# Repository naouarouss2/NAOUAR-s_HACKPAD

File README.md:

**NAOUAR's HACKPAD**

I do a lot of multitasking daily, and that also means that I use a lot of shortcuts, either to switch between apps, or to execute some programs, taks, and commands.
Some of the shortcuts can be pretty sketchy to get to, especially those that have buttons very far apart on the keyboard and require you to get your right hand off the mouse.
So to solve all of that, I decided to make a HACKPAD that has 12 programmable switches, a switch to switch between 4 keymaps, an encoder, an OLED display, and of course RGB.

I designed the PCB on KiCad, so here is the schematics :

And here is the PCB :

Everything will go inside this 3D Printed enclosure :

It will be mounted using M3*16 screws and heatset inserts just like shown below :

The bottom part of the enclosure will be printed in very thin white, or in transparent resin (if allowed), so that we can get the RGB underglow designed in the PCB.

The code is still untested, but I will test it as soon as I get my hands on the electronics, and correct the errors and do the mapping.

**BOM :**

1 SEED XIAO RP2040 (through-hole version)

13 MX switches

13 DSA Keycaps

1 EC11 Encoder

16 1N4148 Diodes

15 SK6812 Mini LEDs

1 0.91 inch 128*32 OLED Display

4 M3-16 screws

4 M3 heatset inserts

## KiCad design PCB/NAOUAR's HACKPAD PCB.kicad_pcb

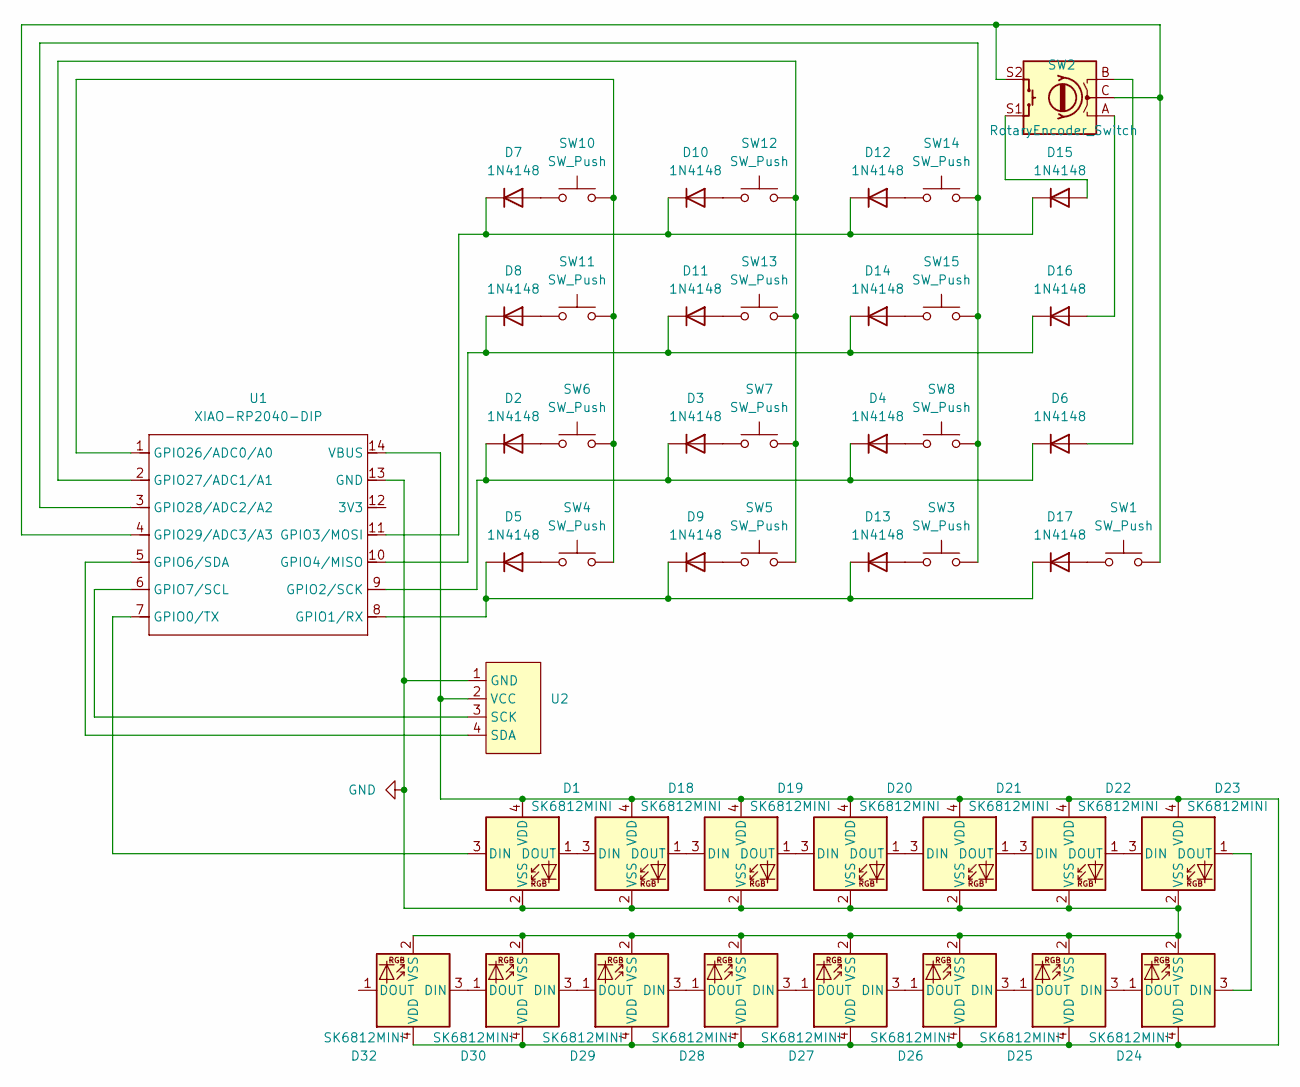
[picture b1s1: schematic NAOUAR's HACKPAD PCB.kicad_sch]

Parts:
D1, D18, D19, D20, D21, D22, D23, D24, D25, D26, D27, D28, D29, D30, D32: SK6812MINI; LED_SK6812MINI_PLCC4_3.5x3.5mm_P1.75mm
D2, D3, D4, D5, D6, D7, D8, D9, D10, D11, D12, D13, D14, D15, D16, D17: 1N4148; D_DO-35_SOD27_P7.62mm_Horizontal
SW1, SW3, SW4, SW5, SW6, SW7, SW8, SW10, SW11, SW12, SW13, SW14, SW15: SW_Push; SW_Cherry_MX_1.00u_PCB
SW2: RotaryEncoder_Switch; RotaryEncoder_Alps_EC11E-Switch_Vertical_H20mm
U1: XIAO-RP2040-DIP
U2: SSD1306-0.91-OLED-4pin-128x32

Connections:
GND: D1.2 (VSS), D18.2 (VSS), D19.2 (VSS), D20.2 (VSS), D21.2 (VSS), D22.2 (VSS), D23.2 (VSS), D24.2 (VSS), D25.2 (VSS), D26.2 (VSS), D27.2 (VSS), D28.2 (VSS), D29.2 (VSS), D30.2 (VSS), D32.2 (VSS), U1.13 (GND), U2.1 (GND)
unnamed: D1.3 (DIN), U1.7 (GPIO0/TX)
unnamed: D1.1 (DOUT), D18.3 (DIN)
unnamed: D1.4 (VDD), D18.4 (VDD), D19.4 (VDD), D20.4 (VDD), D21.4 (VDD), D22.4 (VDD), D23.4 (VDD), D24.4 (VDD), D25.4 (VDD), D26.4 (VDD), D27.4 (VDD), D28.4 (VDD), D29.4 (VDD), D30.4 (VDD), D32.4 (VDD), U1.14 (VBUS), U2.2 (VCC)
unnamed: D2.2 (A), SW6.1
unnamed: D2.1 (K), D3.1 (K), D4.1 (K), D6.1 (K), U1.9 (GPIO2/SCK)
unnamed: D3.2 (A), SW7.1
unnamed: D4.2 (A), SW8.1
unnamed: D5.2 (A), SW4.1
unnamed: D6.2 (A), SW2.B
unnamed: D7.2 (A), SW10.1
unnamed: D8.2 (A), SW11.1
unnamed: D9.2 (A), SW5.1
unnamed: D10.2 (A), SW12.1
unnamed: D7.1 (K), D10.1 (K), D12.1 (K), D15.1 (K), U1.11 (GPIO3/MOSI)
unnamed: D11.2 (A), SW13.1
unnamed: D8.1 (K), D11.1 (K), D14.1 (K), D16.1 (K), U1.10 (GPIO4/MISO)
unnamed: D12.2 (A), SW14.1
unnamed: D13.2 (A), SW3.1
unnamed: D5.1 (K), D9.1 (K), D13.1 (K), D17.1 (K), U1.8 (GPIO1/RX)
unnamed: D14.2 (A), SW15.1
unnamed: D15.2 (A), SW2.S1
unnamed: D16.2 (A), SW2.A
unnamed: D17.2 (A), SW1.1
unnamed: D18.1 (DOUT), D19.3 (DIN)
unnamed: D19.1 (DOUT), D20.3 (DIN)
unnamed: D20.1 (DOUT), D21.3 (DIN)
unnamed: D21.1 (DOUT), D22.3 (DIN)
unnamed: D22.1 (DOUT), D23.3 (DIN)
unnamed: D23.1 (DOUT), D24.3 (DIN)
unnamed: D24.1 (DOUT), D25.3 (DIN)
unnamed: D25.1 (DOUT), D26.3 (DIN)
unnamed: D26.1 (DOUT), D27.3 (DIN)
unnamed: D27.1 (DOUT), D28.3 (DIN)
unnamed: D28.1 (DOUT), D29.3 (DIN)
unnamed: D29.1 (DOUT), D30.3 (DIN)
unnamed: D30.1 (DOUT), D32.3 (DIN)
unnamed: U1.5 (GPIO6/SDA), U2.4 (SDA)
unnamed: U1.6 (GPIO7/SCL), U2.3 (SCK)
unnamed: SW4.2, SW6.2, SW10.2, SW11.2, U1.1 (GPIO26/ADC0/A0)
unnamed: SW5.2, SW7.2, SW12.2, SW13.2, U1.2 (GPIO27/ADC1/A1)
unnamed: SW3.2, SW8.2, SW14.2, SW15.2, U1.3 (GPIO28/ADC2/A2)
unnamed: SW1.2, SW2.C, SW2.S2, U1.4 (GPIO29/ADC3/A3)

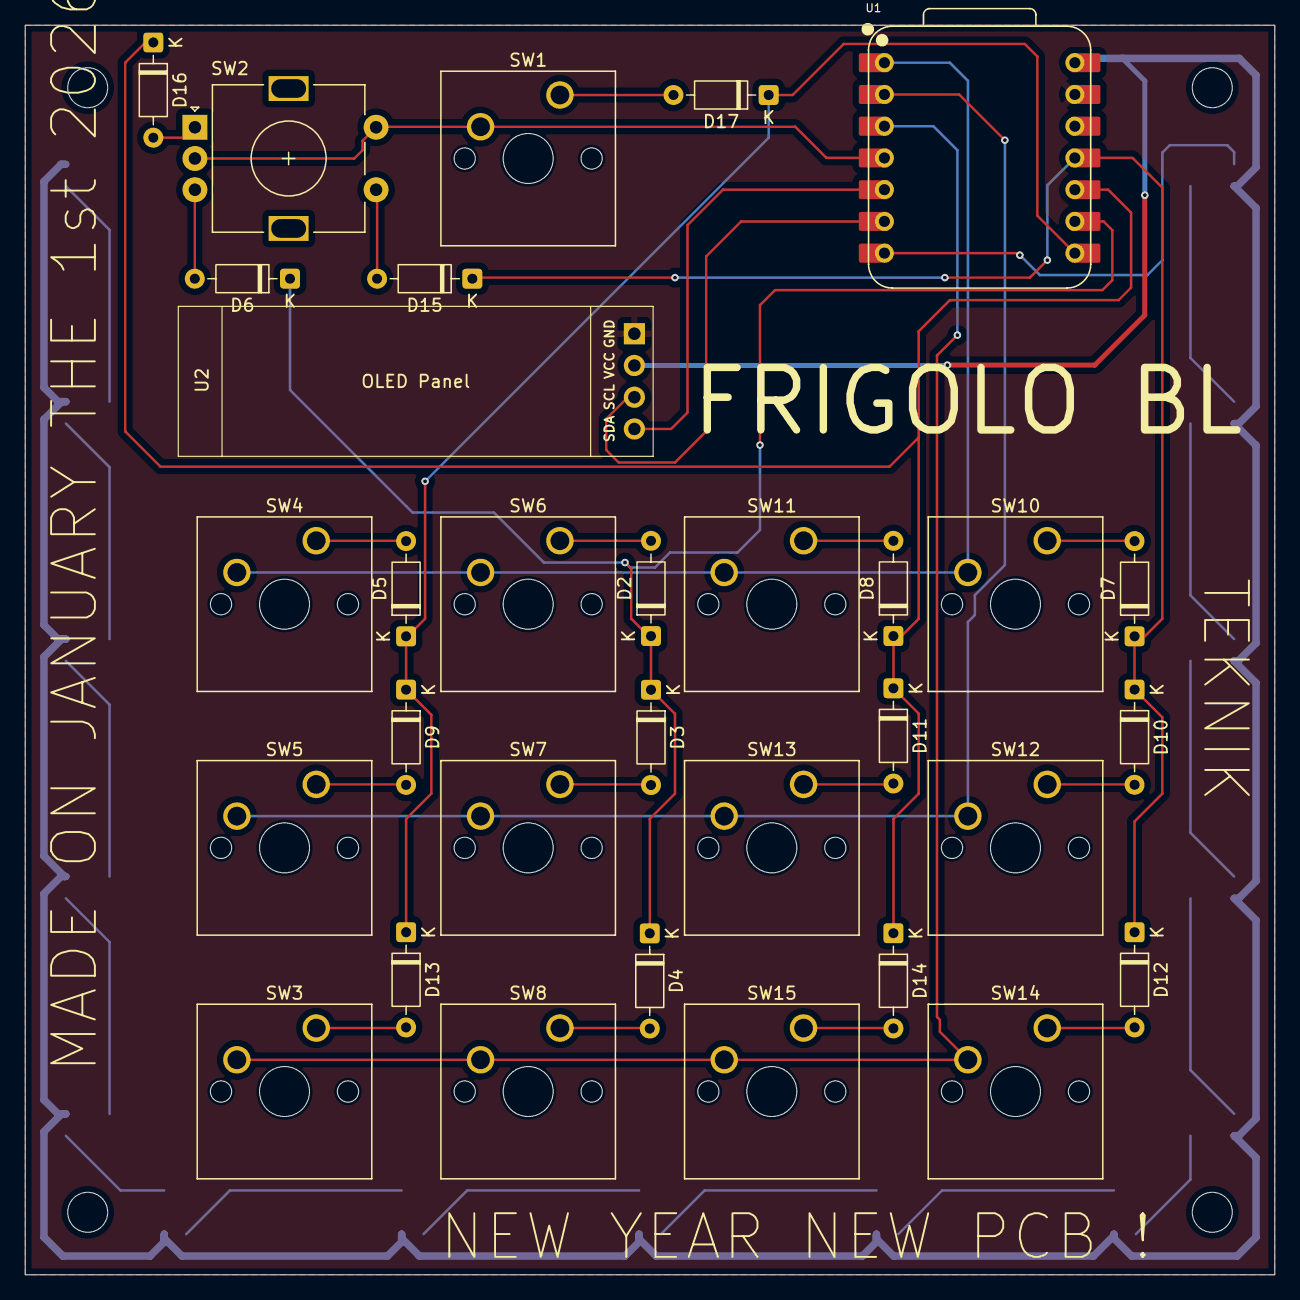
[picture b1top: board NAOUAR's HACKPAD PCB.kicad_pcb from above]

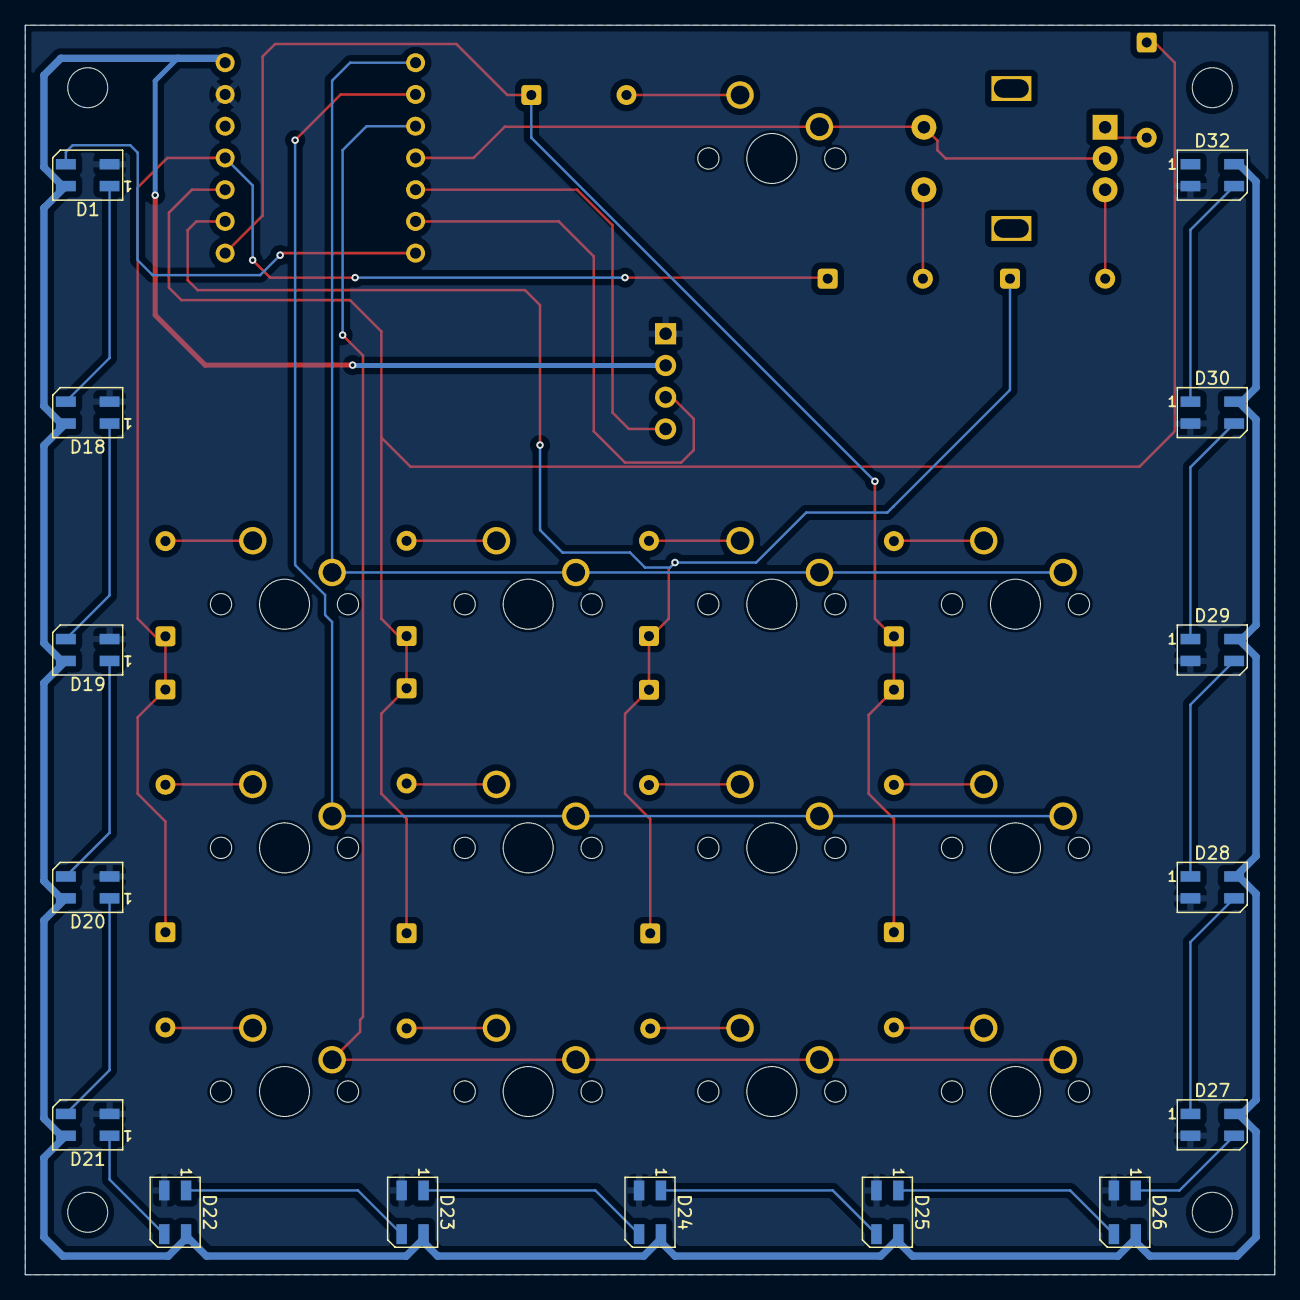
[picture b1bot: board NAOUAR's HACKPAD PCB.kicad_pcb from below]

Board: 4 copper layers, 100.0 x 100.0 mm, 47 parts (15 on the bottom side), 43 nets.

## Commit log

2026-01-04 Add README
